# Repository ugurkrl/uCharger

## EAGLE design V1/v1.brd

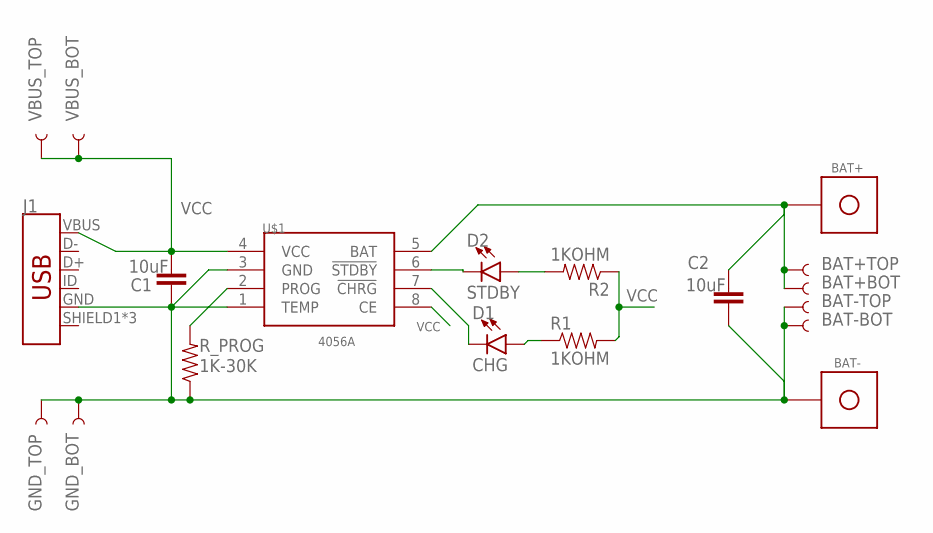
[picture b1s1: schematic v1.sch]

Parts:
BAT+: BAT_TAB; BATT_TAB
BAT+BOT: TEST-POINT3; PAD.03X.03
BAT+TOP: TEST-POINT3; PAD.03X.03
BAT-: BAT_TAB; BATT_TAB
BAT-BOT: TEST-POINT3; PAD.03X.03
BAT-TOP: TEST-POINT3; PAD.03X.03
C1, C2: 10uF; 0402
D1: CHG; LED-0603
D2: STDBY; LED-0603
GND_BOT: TEST-POINT3; PAD.03X.03
GND_TOP: TEST-POINT3; PAD.03X.03
J1: USB_MICRO-B_FEMALE-SMT; USB-B-MICRO-SMD
R1, R2: 1KOHM; 0402
R_PROG: 1K-30K; 0402
U$1: 4056A; SOP-8
VBUS_BOT: TEST-POINT3; PAD.03X.03
VBUS_TOP: TEST-POINT3; PAD.03X.03

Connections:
unnamed: R_PROG.2, U$1.2 (PROG)
unnamed: BAT-.P$1, BAT-BOT.P$1, BAT-TOP.P$1, C1.2, C2.2, GND_BOT.P$1, GND_TOP.P$1, J1.GND, R_PROG.1, U$1.1 (TEMP), U$1.3 (GND)
unnamed: D2.C, U$1.6 (!STDBY)
unnamed: D1.C, U$1.7 (!CHRG)
unnamed: D2.A, R2.2
unnamed: D1.A, R1.1
unnamed: BAT+.P$1, BAT+BOT.P$1, BAT+TOP.P$1, C2.1, U$1.5 (BAT)
VCC: C1.1, J1.VBUS, R1.2, R2.1, U$1.4 (VCC), U$1.8 (CE), VBUS_BOT.P$1, VBUS_TOP.P$1

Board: 2 copper layers, 19 parts (8 on the bottom side), 8 nets, no tracks yet.

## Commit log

2019-08-14 V1 : initial commit

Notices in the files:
parts and their libraries:
SparkFun-Capacitors: Licensing: Creative Commons ShareAlike 4.0 International - https://creativecommons.org/licenses/by-sa/4.0
